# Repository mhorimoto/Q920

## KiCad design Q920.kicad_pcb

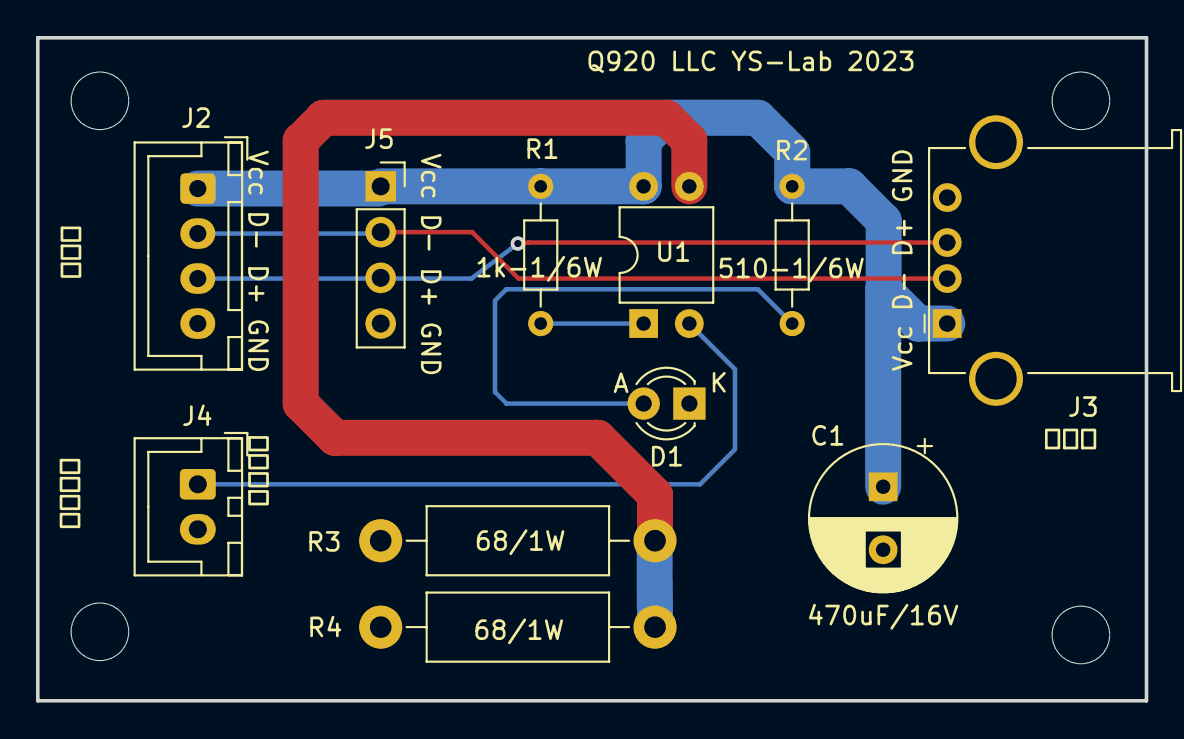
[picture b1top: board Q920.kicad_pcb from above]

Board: 2 copper layers, 61.6 x 36.8 mm, 11 parts (0 on the bottom side), 8 nets.

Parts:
C1: 470uF/16V; CP_Radial_D8.0mm_P3.50mm
D1: OSG8HA3Z74A; LED_D3.0mm
J2: XH-B4B; JST_XH_B4B-XH-A_1x04_P2.50mm_Vertical
J3: 出力側 USB_A; USB_A_Stewart_SS-52100-001_Horizontal
J4: SW pin/Conn_01x02_Socket; JST_XH_B2B-XH-A_1x02_P2.50mm_Vertical
J5: TEST POINT; PinSocket_1x04_P2.54mm_Vertical
R1: 1k-1/6W; R_Axial_DIN0204_L3.6mm_D1.6mm_P7.62mm_Horizontal
R2: 510-1/6W; R_Axial_DIN0204_L3.6mm_D1.6mm_P7.62mm_Horizontal
R3, R4: 68/1W; R_Axial_DIN0411_L9.9mm_D3.6mm_P15.24mm_Horizontal
U1: TLP222A; DIP-4_W7.62mm

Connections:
/D+: J2.3, J3.3 (D+), J5.3
/D-: J2.2, J3.2 (D-), J5.2
/VBUS: C1.1, J2.1, J3.1 (VBUS), J5.1, R1.1, R2.1, U1.4
GND: C1.2, D1.1 (K), J2.4, J3.4 (GND), J3.5 (Shield), J4.2, J5.4, R3.2, R4.2
unnamed: D1.2 (A), R2.2
unnamed: J4.1, U1.2
unnamed: R1.2, U1.1
unnamed: R3.1, R4.1, U1.3

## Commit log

2023-11-20 sche: 不要な配線を消す。ドキュメント整備
2023-11-20 PCB基板化
2023-11-27 cad: リレーを抵抗に変更した
2023-11-27 rel: ver 2.00
2023-11-27 pcb: 社名変更
